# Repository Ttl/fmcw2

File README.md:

FMCW radar hardware, firmware and processing software.

Folders:

hardware: KiCad hardware design files.

- fmcw2: RF board.
- fmcw2_mcu: Digital board.

firmware: 
- Firmware for LPC4320 microcontroller. Based on [HackRF](https://github.com/mossmann/hackrf) firmware.

host: 
- Host programs for recording data, programming firmware. Also from HackRF with small modifications.

processing:
- fir: Resamples, filters and repackages samples for other programs.
- filter.py: Output FIR filter coefficients for fir C program.
- analysis.py: Various analyses about the recorded data.
- sar_bicycle.py: Pre-processing of raw data.
- sar_process.py: Focus raw data to SAR image.
- sar_autofocus.py: Simple minimum entropy autofocusing of SAR image.

SAR focusing program is loosely based on Matlab program by Gregory L. Charvat
and it also includes some functions from [RITSAR](https://github.com/dm6718/RITSAR).

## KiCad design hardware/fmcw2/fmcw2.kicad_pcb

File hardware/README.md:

PCB info:

OSH Park 4-layer.

Material: FR408

Relative permittivity: 3.66

Tangent delta: 0.0127

Stackup:

- 1 mil solder resist
- 1 oz copper (1.4 mil)
- 6.7 mil prepreg
- 0.5 oz copper (0.7 mil)
- 47 mil core
- 0.5 oz copper (0.7 mil)
- 6.7 mil prepreg
- 1 oz copper (1.4 mil)
- 1 mil solder resist

More information: http://support.oshpark.com/support/solutions/articles/122263-4-layer-board-stackup-and-specifications

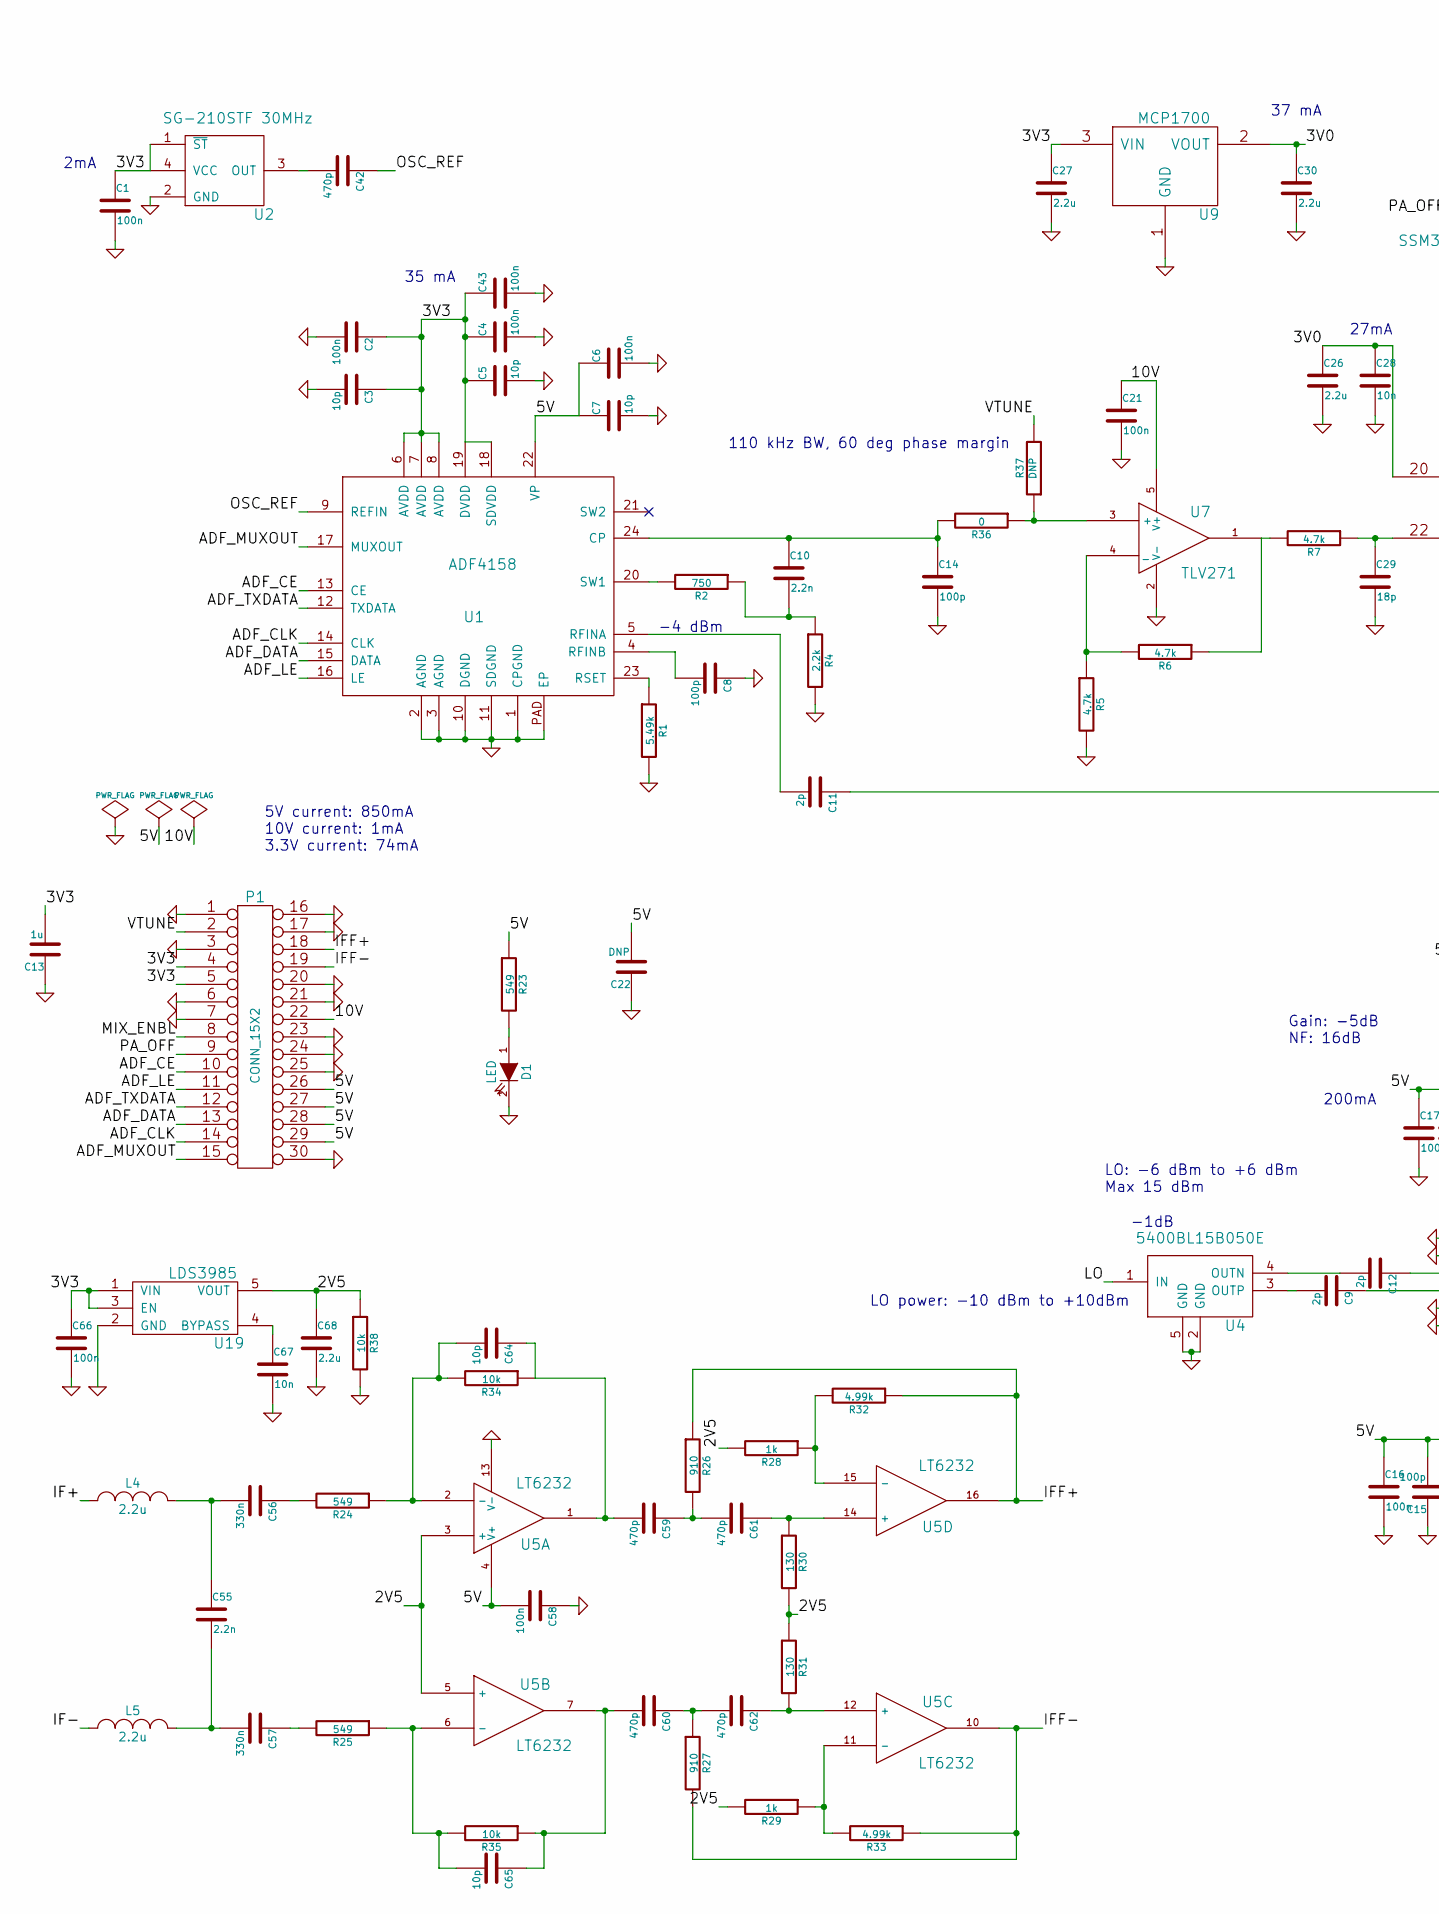
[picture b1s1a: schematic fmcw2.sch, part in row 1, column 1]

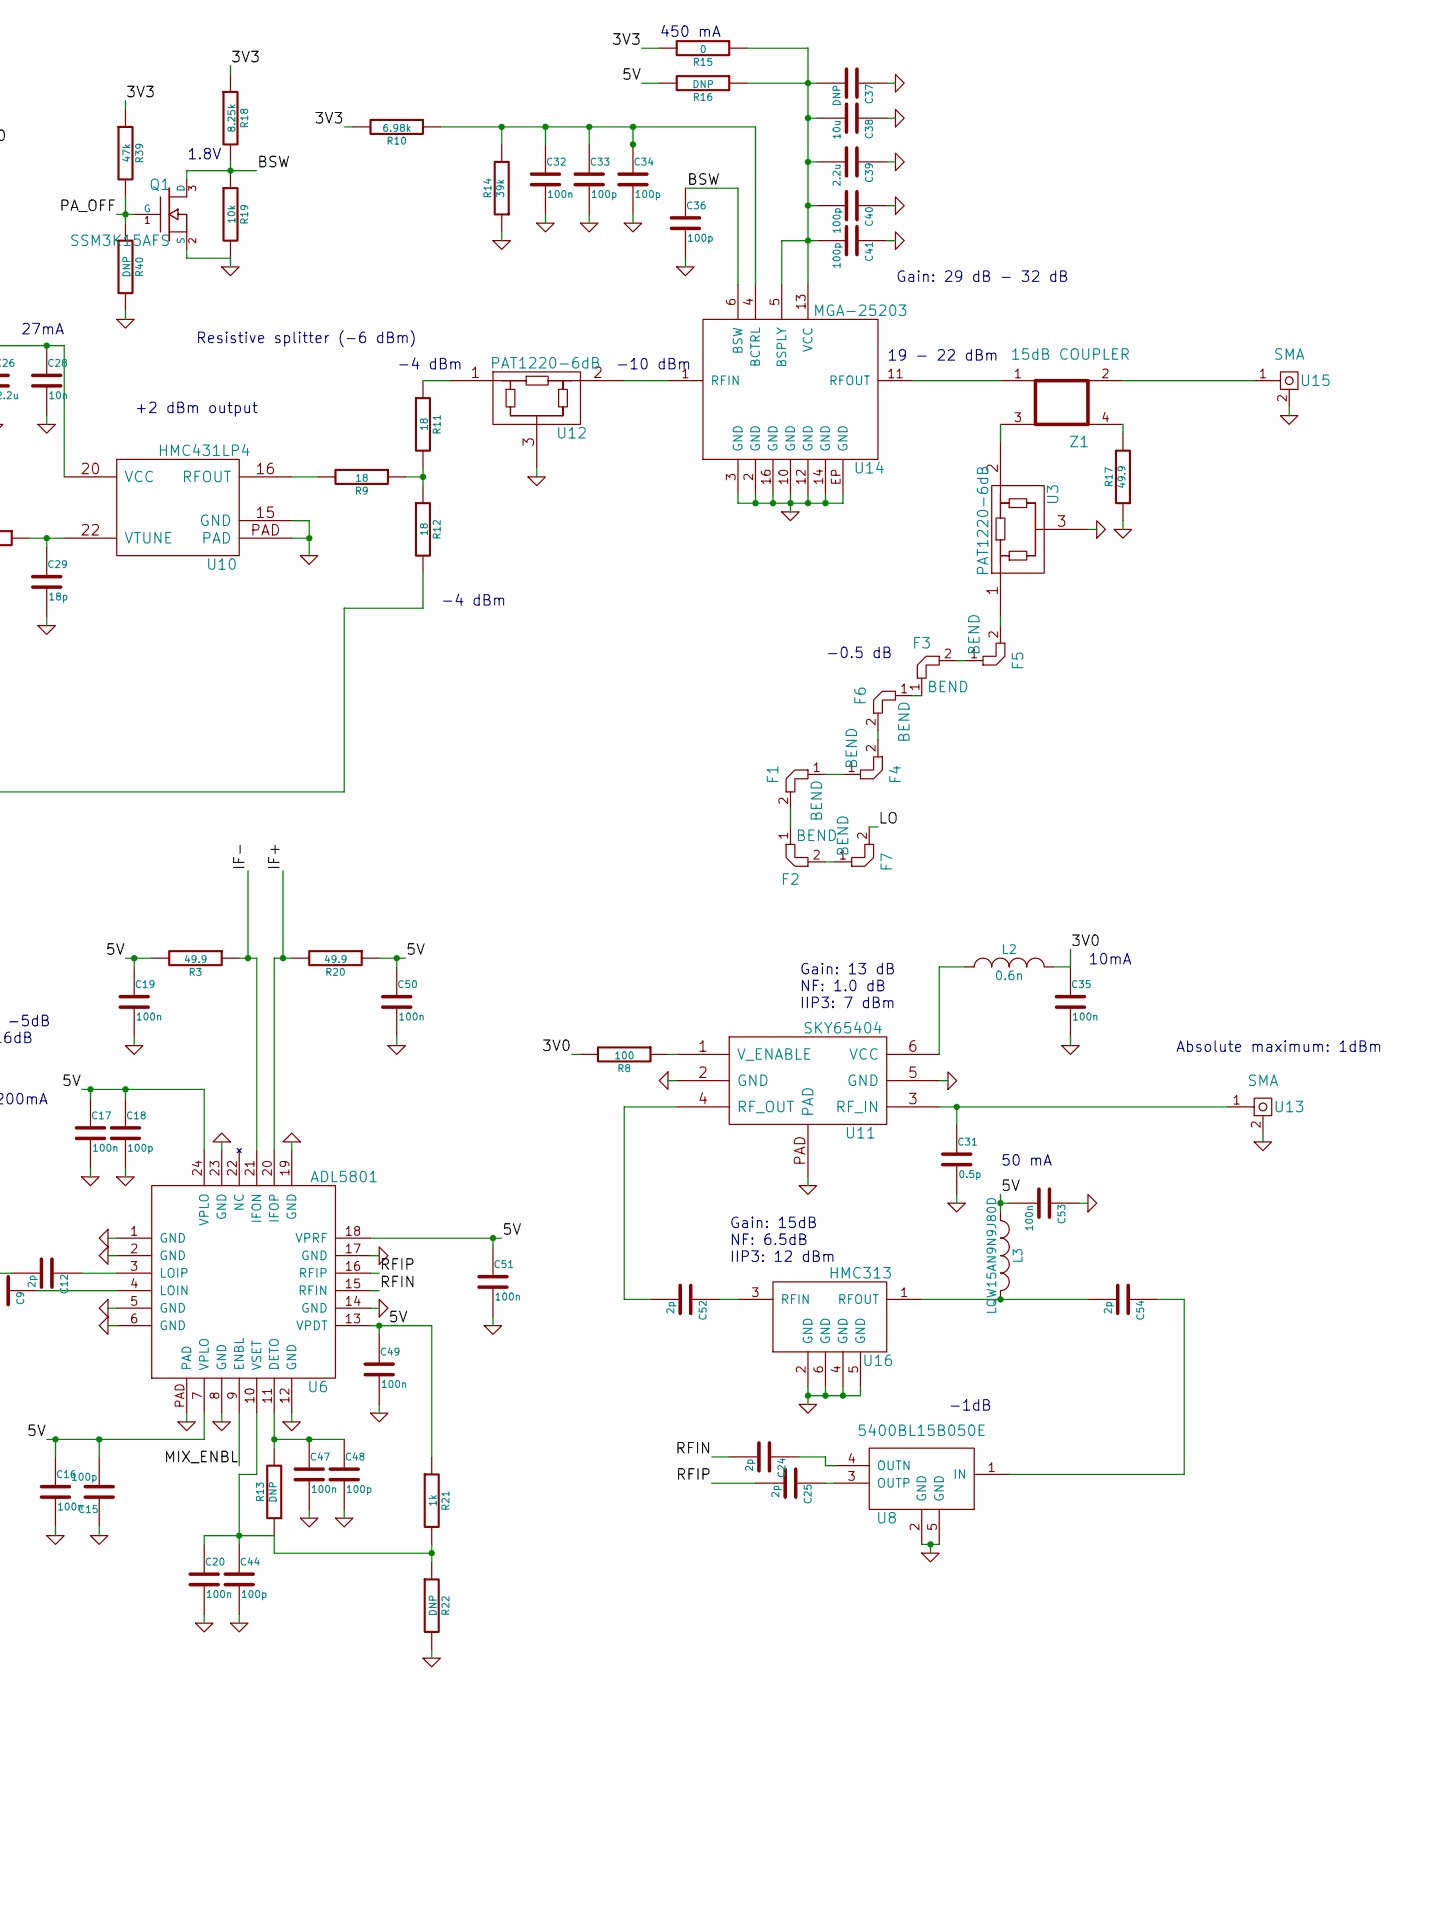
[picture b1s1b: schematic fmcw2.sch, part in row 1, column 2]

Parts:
C1, C2, C4, C6, C16, C17, C19, C20, C21, C32, C35, C43, C47, C49, C50, C51, C53, C58, C66: 100n; C_0402b
C3, C5, C7, C64, C65: 10p; C_0402b
C8, C14, C15, C18, C33, C34, C36, C40, C41, C44, C48: 100p; C_0402b
C9, C11, C12, C24, C25, C52, C54: 2p; C_0402b
C10, C55: 2.2n; C_0402b
C13: 1u; C_0603b
C22: DNP; C_0805b
C26, C27, C30, C39, C68: 2.2u; C_0603b
C28, C67: 10n; C_0402b
C29: 18p; C_0402b
C31: 0.5p; C_0402b
C37: DNP; C_0603b
C38: 10u; C_0805b
C42, C59, C60, C61, C62: 470p; C_0402b
C56, C57: 330n; C_0603b
D1: LED; LED_0603
F1, F2, F7: BEND; uwmiter_0.34_0.17_90
F3, F4, F5, F6: BEND; uwmiter_0.34_0.17_45
L2: 0.6n; C_0402
L3: LQW15AN9N9J80D; C_0402
L4, L5: 2.2u; C_0402
P1: CONN_15X2; DF12B(5.0)-30DP-0.5V(86)
Q1: SSM3K15AFS; SOT-416
R1: 5.49k; R_0402b
R2: 750; R_0402b
R3, R17, R20: 49.9; R_0402b
R4: 2.2k; R_0402b
R5, R6, R7: 4.7k; R_0402b
R8: 100; R_0402b
R9, R11, R12: 18; R_0402b
R10: 6.98k; R_0402b
R13, R16, R22, R37, R40: DNP; R_0402b
R14: 39k; R_0402b
R15, R36: 0; R_0402b
R18: 8.25k; R_0402b
R19, R34, R35, R38: 10k; R_0402b
R21, R28, R29: 1k; R_0402b
R23, R24, R25: 549; R_0402b
R26, R27: 910; R_0402b
R30, R31: 130; R_0402b
R32, R33: 4.99k; R_0402b
R39: 47k; R_0402b
U1: ADF4158; VFQFN-24
U2: SG-210STF 30MHz; SG-210STF
U3, U12: PAT1220-6dB; PAT1220
U4, U8: 5400BL15B050E
U5: LT6232; SSOP-16_3.9x4.9mm_Pitch0.635mm
U6: ADL5801; VFQFN-24
U7: TLV271; SOT-23-5
U9: MCP1700; SOT-23
U10: HMC431LP4; VQFN-24
U11: SKY65404; XFDFN-6
U13, U15: SMA; CONSMA003.062
U14: MGA-25203
U16: HMC313; SOT-23-6
U19: LDS3985; SOT-23-5L
Z1: 15dB COUPLER; coupler

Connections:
/2V5: C68.1, R28.2, R29.2, R30.2, R31.1, R38.1, U5.3 (+), U5.5 (+), U19.5 (VOUT)
/3V0: C26.1, C28.1, C30.1, C35.1, L2.2, R8.2, U9.2 (VOUT), U10.20 (VCC)
/3V3: C1.1, C2.1, C3.1, C4.1, C5.1, C13.2, C27.1, C43.1, C66.1, P1.4, P1.5, R10.2, R15.2, R18.1, R39.1, U1.6 (AVDD), U1.7 (AVDD), U1.8 (AVDD), U1.18 (SDVDD), U1.19 (DVDD), U2.1 (~ST), U2.4 (VCC), U9.3 (VIN), U19.1 (VIN), U19.3 (EN)
/5V: C6.1, C7.1, C15.2, C16.1, C17.1, C18.1, C19.1, C22.2, C49.1, C50.1, C51.1, C53.2, C58.2, L3.1, P1.26, P1.27, P1.28, P1.29, R3.2, R16.2, R20.1, R21.1, R23.1, U1.22 (VP), U5.4 (V+), U6.7 (VPLO), U6.13 (VPDT), U6.18 (VPRF), U6.24 (VPLO)
/10V: C21.1, P1.22, U7.5 (V+)
/ADF_CE: P1.10, U1.13 (CE)
/ADF_CLK: P1.14, U1.14 (CLK)
/ADF_DATA: P1.13, U1.15 (DATA)
/ADF_LE: P1.11, U1.16 (LE)
/ADF_MUXOUT: P1.15, U1.17 (MUXOUT)
/ADF_TXDATA: P1.12, U1.12 (TXDATA)
/BSW: C36.1, Q1.3 (D), R18.2, R19.1, U14.6 (BSW)
/IF+: L4.1, R20.2, U6.20 (IFOP)
/IF-: L5.1, R3.1, U6.21 (IFON)
/IFF+: P1.18, R26.1, R32.1, U5.16
/IFF-: P1.19, R27.2, R33.1, U5.10
/LO: F7.2, U4.1 (IN)
/MIX_ENBL: P1.8, U6.9 (ENBL)
/OSC_REF: C42.1, U1.9 (REFIN)
/PA_OFF: P1.9, Q1.1 (G), R39.2, R40.1
/RFIN: C24.2, U6.15 (RFIN)
/RFIP: C25.2, U6.16 (RFIP)
/VTUNE: P1.2, R37.2
GND: C1.2, C2.2, C3.2, C4.2, C5.2, C6.2, C7.2, C8.1, C13.1, C14.2, C15.1, C16.2, C17.2, C18.2, C19.2, C20.2, C21.2, C22.1, C26.2, C27.2, C28.2, C29.2, C30.2, C31.2, C32.2, C33.2, C34.2, C35.2, C36.2, C37.1, C38.1, C39.1, C40.1, C41.1, C43.2, C44.2, C47.2, C48.2, C49.2, C50.2, C51.2, C53.1, C58.1, C66.2, C67.2, C68.2, D1.2 (K), P1.1, P1.3, P1.6, P1.7, P1.16, P1.17, P1.20, P1.21, P1.23, P1.24, P1.25, P1.30, Q1.2 (S), R1.2, R4.2, R5.2, R14.1, R17.1, R19.2, R22.2, R38.2, R40.2, U1.1 (CPGND), U1.2 (AGND), U1.3 (AGND), U1.10 (DGND), U1.11 (SDGND), U1.PAD (EP), U2.2 (GND), U3.3, U4.2 (GND), U4.5 (GND), U5.13 (V-), U6.1 (GND), U6.2 (GND), U6.5 (GND), U6.6 (GND), U6.8 (GND), U6.12 (GND), U6.14 (GND), U6.17 (GND), U6.19 (GND), U6.23 (GND), U6.PAD, U7.2 (V-), U8.2 (GND), U8.5 (GND), U9.1 (GND), U10.15 (GND), U10.PAD, U11.2 (GND), U11.5 (GND), U11.PAD, U12.3, U13.2, U14.2 (GND), U14.3 (GND), U14.10 (GND), U14.12 (GND), U14.14 (GND), U14.16 (GND), U14.EP (GND), U15.2, U16.2 (GND), U16.4 (GND), U16.5 (GND), U16.6 (GND), U19.2 (GND)
unnamed: C8.2, U1.4 (RFINB)
unnamed: C9.1, U6.4 (LOIN)
unnamed: C9.2, U4.3 (OUTP)
unnamed: C10.1, C14.1, R36.2, U1.24 (CP)
unnamed: C10.2, R2.1, R4.1
unnamed: C11.1, R12.2
unnamed: C11.2, U1.5 (RFINA)
unnamed: C12.1, U6.3 (LOIP)
unnamed: C12.2, U4.4 (OUTN)
unnamed: C20.1, C44.1, R13.1, R21.2, R22.1, U6.10 (VSET)
unnamed: C24.1, U8.4 (OUTN)
unnamed: C25.1, U8.3 (OUTP)
unnamed: C29.1, R7.1, U10.22 (VTUNE)
unnamed: C31.1, U11.3 (RF_IN), U13.1
unnamed: C32.1, C33.1, C34.1, R10.1, R14.2, U14.4 (BCTRL)
unnamed: C37.2, C38.2, C39.2, C40.2, C41.2, R15.1, R16.1, U14.5 (BSPLY), U14.13 (VCC)
unnamed: C42.2, U2.3 (OUT)
unnamed: C47.1, C48.1, R13.2, U6.11 (DETO)
unnamed: C52.1, U16.3 (RFIN)
unnamed: C52.2, U11.4 (RF_OUT)
unnamed: C54.1, U8.1 (IN)
unnamed: C54.2, L3.2, U16.1 (RFOUT)
unnamed: C55.1, C56.2, L4.2
unnamed: C55.2, C57.2, L5.2
unnamed: C56.1, R24.2
unnamed: C57.1, R25.2
unnamed: C59.1, C61.2, R26.2
unnamed: C59.2, C64.1, R34.1, U5.1
unnamed: C60.1, C62.2, R27.1
unnamed: C60.2, C65.1, R35.1, U5.7
unnamed: C61.1, R30.1, U5.14 (+)
unnamed: C62.1, R31.2, U5.12 (+)
unnamed: C64.2, R24.1, R34.2, U5.2 (-)
unnamed: C65.2, R25.1, R35.2, U5.6 (-)
unnamed: C67.1, U19.4 (BYPASS)
unnamed: D1.1 (A), R23.2
unnamed: F1.1, F4.1
unnamed: F1.2, F2.1
unnamed: F2.2, F7.1
unnamed: F3.1, F6.1
unnamed: F3.2, F5.1
unnamed: F4.2, F6.2
unnamed: F5.2, U3.1
unnamed: L2.1, U11.6 (VCC)
unnamed: R1.1, U1.23 (RSET)
unnamed: R2.2, U1.20 (SW1)
unnamed: R5.1, R6.2, U7.4 (_)
unnamed: R6.1, R7.2, U7.1
unnamed: R8.1, U11.1 (V_ENABLE)
unnamed: R9.2, U10.16 (RFOUT)
unnamed: R11.1, U12.1
unnamed: R9.1, R11.2, R12.1
unnamed: R17.2, Z1.4
unnamed: R28.1, R32.2, U5.15 (-)
unnamed: R29.1, R33.2, U5.11 (-)
unnamed: R36.1, R37.1, U7.3 (+)
unnamed: U3.2, Z1.3
unnamed: U12.2, U14.1 (RFIN)
unnamed: U14.11 (RFOUT), Z1.1
unnamed: U15.1, Z1.2

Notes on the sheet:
Resistive splitter (-6 dBm)
+2 dBm output
-4 dBm
27mA
-10 dBm
Gain: 29 dB - 32 dB
19 - 22 dBm
110 kHz BW, 60 deg phase margin
2mA
LO: -6 dBm to +6 dBm Max 15 dBm
35 mA
450 mA
10mA
37 mA
-1dB
1.8V
Gain: 13 dB NF: 1.0 dB IIP3: 7 dBm
Gain: -5dB NF: 16dB
200mA
LO power: -10 dBm to +10dBm
Gain: 15dB NF: 6.5dB IIP3: 12 dBm
50 mA
Absolute maximum: 1dBm
5V current: 850mA 10V current: 1mA 3.3V current: 74mA
-0.5 dB

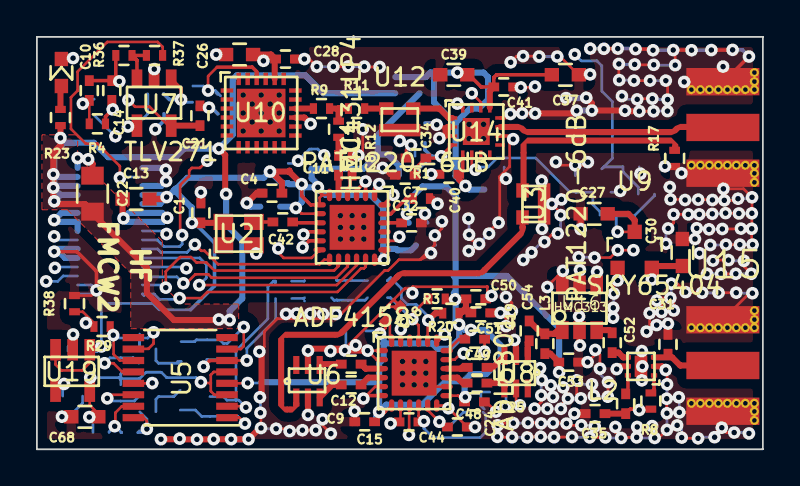
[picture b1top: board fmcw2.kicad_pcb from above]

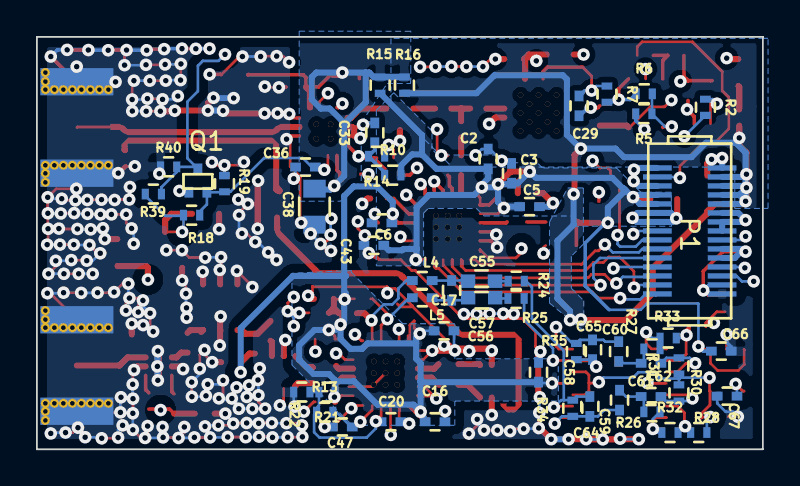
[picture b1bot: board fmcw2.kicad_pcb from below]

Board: 4 copper layers, 40.3 x 22.9 mm, 136 parts (55 on the bottom side), 84 nets.

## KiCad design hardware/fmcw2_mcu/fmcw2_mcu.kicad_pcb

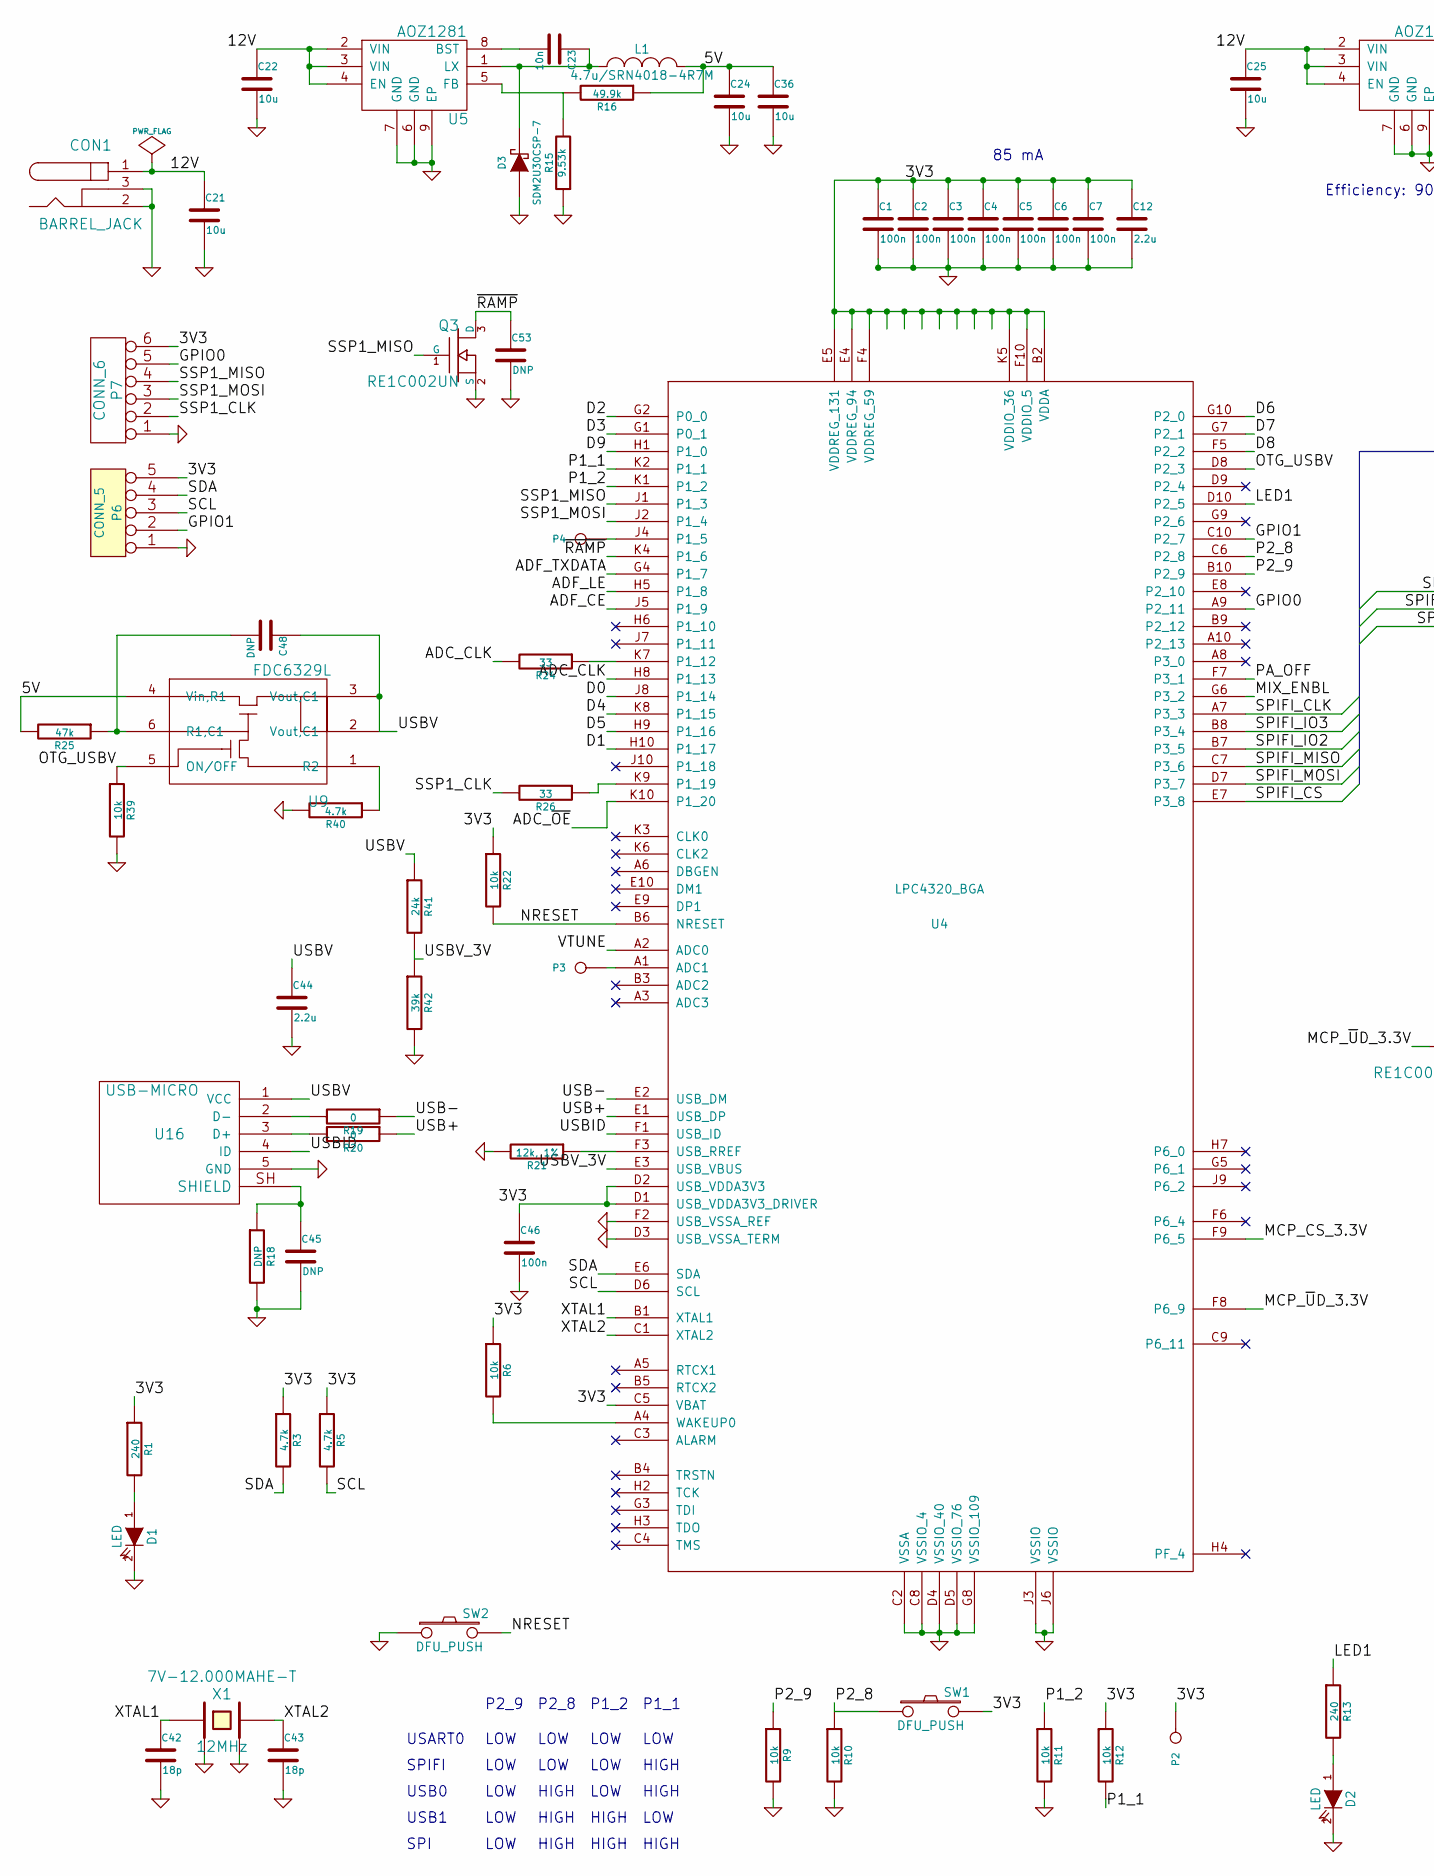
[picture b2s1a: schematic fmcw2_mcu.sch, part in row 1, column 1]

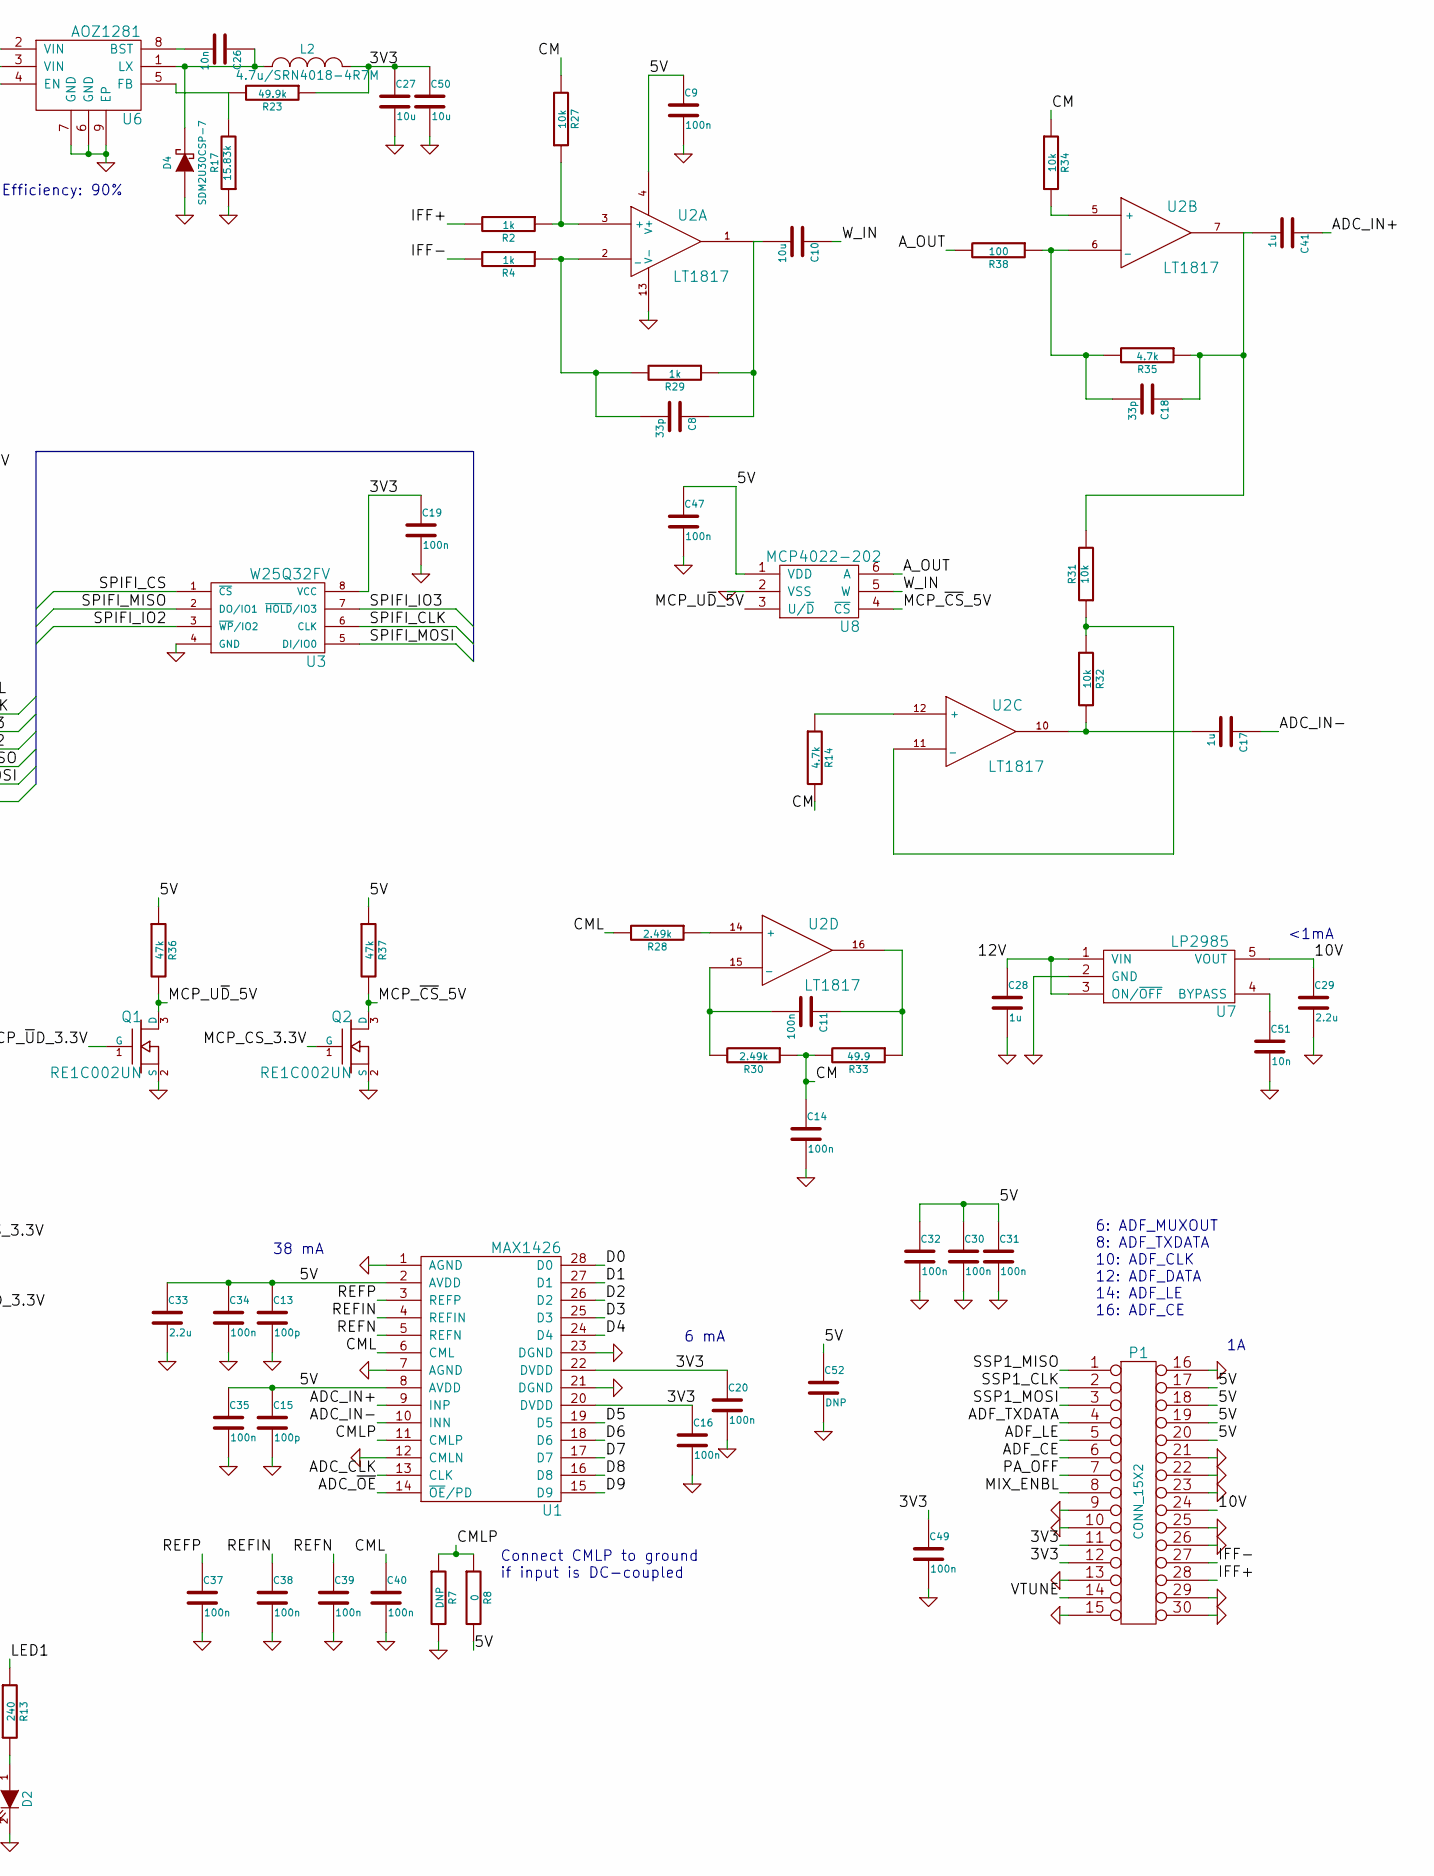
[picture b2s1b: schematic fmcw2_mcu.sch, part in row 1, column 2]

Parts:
C1, C2, C3, C4, C5, C6, C7, C9, C11, C14, C16, C19, C20, C30, C31, C32, C34, C35, C37, C38, C39, C40, C46, C47, C49: 100n; C_0402b
C8, C18: 33p; C_0402b
C10, C21, C22, C24, C25, C27, C36, C50: 10u; C_0805b
C12, C29, C33, C44: 2.2u; C_0603b
C13, C15: 100p; C_0402b
C17, C28, C41: 1u; C_0603b
C23, C26, C51: 10n; C_0402b
C42, C43: 18p; C_0402b
C45, C48, C53: DNP; C_0402b
C52: DNP; C_0603b
CON1: BARREL_JACK; EJ508A
D1, D2: LED; LED_0603
D3, D4: SDM2U30CSP-7; XDFN-2
L1, L2: 4.7u/SRN4018-4R7M; SRN4018
P1: CONN_15X2; DF12A-30DS-0.5V(81)
P2, P3, P4: CONN_1; TP_1.00
P6: CONN_5; Pin_Header_Straight_1x05
P7: CONN_6; Pin_Header_Straight_1x06
Q1, Q2, Q3: RE1C002UN; SOT-416
R1, R13: 240; R_0402b
R2, R4, R29: 1k; R_0402b
R3, R5, R14, R35, R40: 4.7k; R_0402b
R6, R9, R10, R11, R12, R22, R27, R31, R32, R34, R39: 10k; R_0402b
R7, R18: DNP; R_0402b
R8, R19, R20: 0; R_0402b
R15: 9.53k; R_0402b
R16, R23: 49.9k; R_0402b
R17: 15.83k; R_0402b
R21: 12k, 1%; R_0402b
R24, R26: 33; R_0402b
R25, R36, R37: 47k; R_0402b
R28, R30: 2.49k; R_0402b
R33: 49.9; R_0402b
R38: 100; R_0402b
R41: 24k; R_0402b
R42: 39k; R_0402b
SW1, SW2: DFU_PUSH; EVP-AWBA2A
U1: MAX1426; SSOP-28_5.3x10.2mm_Pitch0.65mm
U2: LT1817; SSOP-16_3.9x4.9mm_Pitch0.635mm
U3: W25Q32FV; SOIJ-8_5.3x5.3mm_Pitch1.27mm
U4: LPC4320_BGA; TFBGA-100
U5, U6: AOZ1281; WFDFN-8
U7: LP2985; SOT-23-5
U8: MCP4022-202; SOT-23-6
U9: FDC6329L; SSOT-6
U16: USB-MICRO; USB_MICRO
X1: 12MHz; XTAL_3.2x2.5

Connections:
/3V3: C1.1, C2.1, C3.1, C4.1, C5.1, C6.1, C7.1, C12.1, C16.1, C19.1, C20.1, C27.1, C46.1, C49.1, C50.1, L2.2, P1.11, P1.12, P2.1, P6.5, P7.6, R1.1, R3.1, R5.1, R6.1, R12.1, R22.1, R23.1, SW1.2, U1.20 (DVDD), U1.22 (DVDD), U3.8 (VCC), U4.B2 (VDDA), U4.C5 (VBAT), U4.D1 (USB_VDDA3V3_DRIVER), U4.D2 (USB_VDDA3V3), U4.E4 (VDDREG_94), U4.E5 (VDDREG_131), U4.F4 (VDDREG_59), U4.F10 (VDDIO_5), U4.K5 (VDDIO_36)
/5V: C9.1, C13.1, C15.1, C24.1, C30.1, C31.1, C32.1, C33.1, C34.1, C35.1, C36.1, C47.1, C52.1, L1.2, P1.17, P1.18, P1.19, P1.20, R8.2, R16.1, R25.2, R36.1, R37.1, U1.2 (AVDD), U1.8 (AVDD), U2.4 (V+), U8.1 (VDD), U9.4 (Vin,R1)
/10V: C29.1, P1.24, U7.5 (VOUT)
/12V: C21.1, C22.1, C25.1, C28.1, CON1.1, U5.2 (VIN), U5.3 (VIN), U5.4 (EN), U6.2 (VIN), U6.3 (VIN), U6.4 (EN), U7.1 (VIN), U7.3 (ON/~OFF~)
/ADC_CLK: R24.2, U1.13 (CLK), U4.H8 (P1_13)
/ADC_IN+: C41.1, U1.9 (INP)
/ADC_IN-: C17.1, U1.10 (INN)
/ADC_~OE~: U1.14 (~OE~/PD), U4.K10 (P1_20)
/ADF_CE: P1.6, U4.J5 (P1_9)
/ADF_LE: P1.5, U4.H5 (P1_8)
/ADF_TXDATA: P1.4, U4.G4 (P1_7)
/A_OUT: R38.2, U8.6 (A)
/CM: C14.1, R14.2, R27.2, R30.1, R33.2, R34.1
/CML: C40.1, R28.2, U1.6 (CML)
/CMLP: R7.1, R8.1, U1.11 (CMLP)
/D0: U1.28 (D0), U4.J8 (P1_14)
/D1: U1.27 (D1), U4.H10 (P1_17)
/D2: U1.26 (D2), U4.G2 (P0_0)
/D3: U1.25 (D3), U4.G1 (P0_1)
/D4: U1.24 (D4), U4.K8 (P1_15)
/D5: U1.19 (D5), U4.H9 (P1_16)
/D6: U1.18 (D6), U4.G10 (P2_0)
/D7: U1.17 (D7), U4.G7 (P2_1)
/D8: U1.16 (D8), U4.F5 (P2_2)
/D9: U1.15 (D9), U4.H1 (P1_0)
/GPIO0: P7.5, U4.A9 (P2_11)
/GPIO1: P6.2, U4.C10 (P2_7)
/IFF+: P1.28, R2.2
/IFF-: P1.27, R4.2
/LED1: R13.1, U4.D10 (P2_5)
/MCP_CS_3.3V: Q2.1 (G), U4.F9 (P6_5)
/MCP_U~D~_5V: Q1.3 (D), R36.2, U8.3 (U/~D~)
/MCP_~CS~_5V: Q2.3 (D), R37.2, U8.4 (~CS~)
/MCP_~U~D_3.3V: Q1.1 (G), U4.F8 (P6_9)
/MIX_ENBL: P1.8, U4.G6 (P3_2)
/NRESET: R22.2, SW2.2, U4.B6 (NRESET)
/OTG_USBV: R39.1, U4.D8 (P2_3), U9.5 (ON/OFF)
/P1_1: R12.2, U4.K2 (P1_1)
/P1_2: R11.1, U4.K1 (P1_2)
/P2_8: R10.1, SW1.1, U4.C6 (P2_8)
/P2_9: R9.1, U4.B10 (P2_9)
/PA_OFF: P1.7, U4.F7 (P3_1)
/REFIN: C38.1, U1.4 (REFIN)
/REFN: C39.1, U1.5 (REFN)
/REFP: C37.1, U1.3 (REFP)
/SCL: P6.3, R5.2, U4.D6 (SCL)
/SDA: P6.4, R3.2, U4.E6 (SDA)
/SPIFI_CLK: U3.6 (CLK), U4.A7 (P3_3)
/SPIFI_CS: U3.1 (~CS), U4.E7 (P3_8)
/SPIFI_IO2: U3.3 (~WP~/IO2), U4.B7 (P3_5)
/SPIFI_IO3: U3.7 (~HOLD~/IO3), U4.B8 (P3_4)
/SPIFI_MISO: U3.2 (DO/IO1), U4.C7 (P3_6)
/SPIFI_MOSI: U3.5 (DI/IO0), U4.D7 (P3_7)
/SSP1_CLK: P1.2, P7.2, R26.2
/SSP1_MISO: P1.1, P7.4, Q3.1 (G), U4.J1 (P1_3)
/SSP1_MOSI: P1.3, P7.3, U4.J2 (P1_4)
/USB+: R20.1, U4.E1 (USB_DP)
/USB-: R19.1, U4.E2 (USB_DM)
/USBID: U4.F1 (USB_ID), U16.4 (ID)
/USBV: C44.1, C48.1, R41.1, U9.2 (Vout,C1), U9.3 (Vout,C1), U16.1 (VCC)
/USBV_3V: R41.2, R42.1, U4.E3 (USB_VBUS)
/VTUNE: P1.14, U4.A2 (ADC0)
/W_IN: C10.1, U8.5 (W)
/XTAL1: C42.1, U4.B1 (XTAL1), X1.1
/XTAL2: C43.1, U4.C1 (XTAL2), X1.3
/~RAMP: C53.1, Q3.3 (D), U4.K4 (P1_6)
GND: C1.2, C2.2, C3.2, C4.2, C5.2, C6.2, C7.2, C9.2, C12.2, C13.2, C14.2, C15.2, C16.2, C19.2, C20.2, C21.2, C22.2, C24.2, C25.2, C27.2, C28.2, C29.2, C30.2, C31.2, C32.2, C33.2, C34.2, C35.2, C36.2, C37.2, C38.2, C39.2, C40.2, C42.2, C43.2, C44.2, C45.2, C46.2, C47.2, C49.2, C50.2, C51.2, C52.2, C53.2, CON1.2, CON1.3, D1.2 (K), D2.2 (K), D3.1 (A), D4.1 (A), P1.9, P1.10, P1.13, P1.15, P1.16, P1.21, P1.22, P1.23, P1.25, P1.26, P1.29, P1.30, P6.1, P7.1, Q1.2 (S), Q2.2 (S), Q3.2 (S), R7.2, R9.2, R10.2, R11.2, R15.1, R17.1, R18.2, R21.2, R39.2, R40.2, R42.2, SW2.1, U1.1 (AGND), U1.7 (AGND), U1.12 (CMLN), U1.21 (DGND), U1.23 (DGND), U2.13 (V-), U3.4 (GND), U4.C2 (VSSA), U4.C8 (VSSIO_4), U4.D3 (USB_VSSA_TERM), U4.D4 (VSSIO_40), U4.D5 (VSSIO_76), U4.F2 (USB_VSSA_REF), U4.G8 (VSSIO_109), U4.J3 (VSSIO), U4.J6 (VSSIO), U5.6 (GND), U5.7 (GND), U5.9 (EP), U6.6 (GND), U6.7 (GND), U6.9 (EP), U7.2 (GND), U8.2 (VSS), U16.5 (GND), X1.2, X1.4
unnamed: C8.2, R4.1, R29.2, U2.2 (_)
unnamed: C8.1, C10.2, R29.1, U2.1
unnamed: C11.1, R33.1, U2.16
unnamed: C11.2, R30.2, U2.15 (_)
unnamed: C17.2, R32.2, U2.10
unnamed: C18.1, C41.2, R31.2, R35.1, U2.7
unnamed: C18.2, R35.2, R38.1, U2.6 (_)
unnamed: C23.1, D3.2 (K), L1.1, U5.1 (LX)
unnamed: C23.2, U5.8 (BST)
unnamed: C26.1, D4.2 (K), L2.1, U6.1 (LX)
unnamed: C26.2, U6.8 (BST)
unnamed: C45.1, R18.1, U16.SH (SHIELD)
unnamed: C48.2, R25.1, U9.6 (R1,C1)
unnamed: C51.1, U7.4 (BYPASS)
unnamed: D1.1 (A), R1.2
unnamed: D2.1 (A), R13.2
unnamed: P3.1, U4.A1 (ADC1)
unnamed: P4.1, U4.J4 (P1_5)
unnamed: R2.1, R27.1, U2.3 (+)
unnamed: R6.2, U4.A4 (WAKEUP0)
unnamed: R14.1, U2.12 (+)
unnamed: R15.2, R16.2, U5.5 (FB)
unnamed: R17.2, R23.2, U6.5 (FB)
unnamed: R19.2, U16.2 (D-)
unnamed: R20.2, U16.3 (D+)
unnamed: R21.1, U4.F3 (USB_RREF)
unnamed: R24.1, U4.K7 (P1_12)
unnamed: R26.1, U4.K9 (P1_19)
unnamed: R28.1, U2.14 (+)
unnamed: R31.1, R32.1, U2.11 (_)
unnamed: R34.2, U2.5 (+)
unnamed: R40.1, U9.1 (R2)

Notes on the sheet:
LOW
P2_9
P2_8
P1_2
P1_1
SPIFI
USART0
HIGH
USB0
USB1
SPI
6: ADF_MUXOUT 8: ADF_TXDATA 10: ADF_CLK 12: ADF_DATA 14: ADF_LE 16: ADF_CE
38 mA
6 mA
Efficiency: 90%
85 mA
<1mA
Connect CMLP to ground if input is DC-coupled

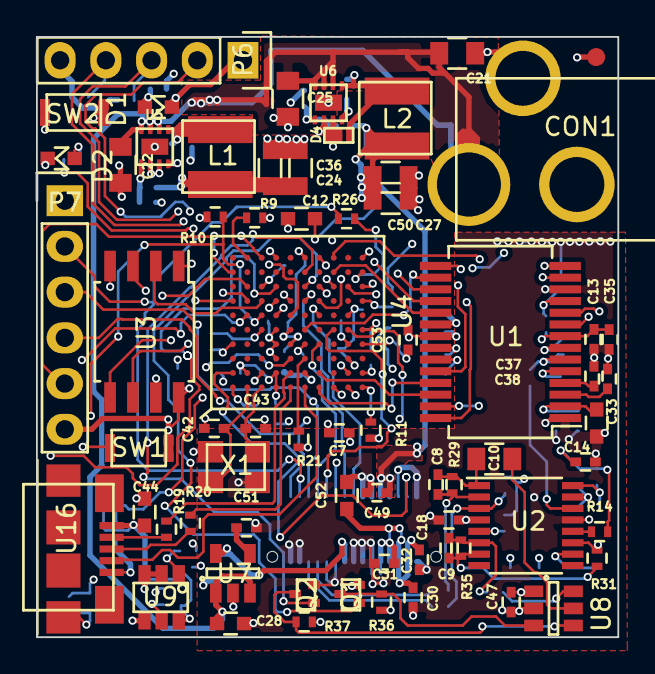
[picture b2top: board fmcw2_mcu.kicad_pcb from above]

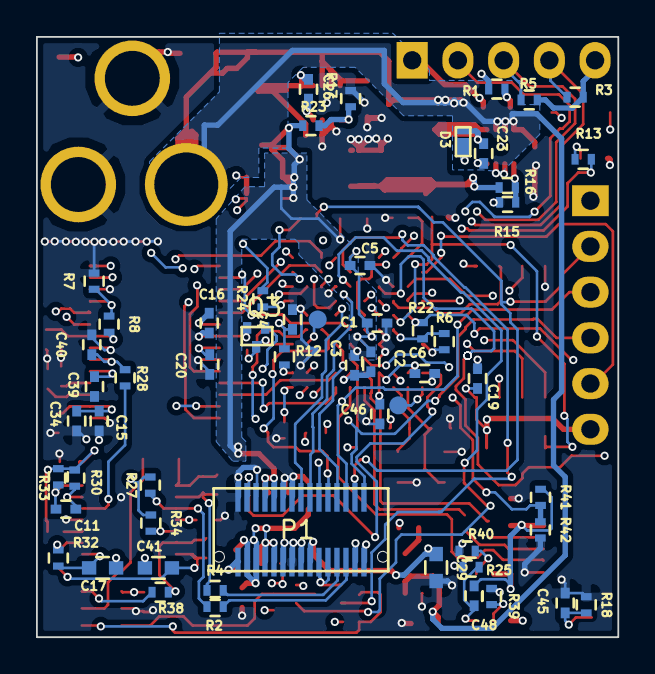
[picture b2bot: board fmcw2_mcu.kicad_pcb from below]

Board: 4 copper layers, 32.3 x 33.3 mm, 124 parts (56 on the bottom side), 99 nets.

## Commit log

2015-07-23 Initial firmware commit
2015-07-27 PC GUI initial commit
2015-07-27 Use pyqtgraph for plotting
2015-07-28 Big plot for range
2015-08-10 Add gitignore
2015-08-10 Update PC program
    Menus, new architecture, add old FMCW radar
2015-08-16 Update firmware
2015-08-18 Add python scripts
2015-08-29 Use all 10bits from ADC
    Add some forgotten files.
2015-08-29 Add C tools
2015-08-29 Add filtering + decimation tool
2015-08-29 Fix filtering script
2015-08-30 Update processing scripts for sync bits
2015-08-30 Send sync words
    Needs jump wire from SSP1_MISO to P5.
    Uses the ramp complete signal from ADF4158 to synchronize the ramps.
2015-09-06 Update processing programs
    Multithreaded file writing in transfer program
    Add header to saved files
    Enable pullup in ramp complete input pin
2015-09-12 Fix off-by-one mistake causing data corruption
2015-10-13 Update various files
2015-10-13 Add hardware design files
2015-10-13 Add program for finding sweeps with invalid length
2015-10-13 Add program for processing bicycle SAR data
2015-10-13 Add SAR focusing program
2015-10-13 Add SAR autofocusing program
2015-10-13 Remove unused GUI, move fir program to processing folder
2015-10-13 Add PDF of schematic
2015-10-14 Add Readme
2015-10-14 Fix Readme formatting
2015-10-14 Fix Readme formatting again
2015-10-14 Fix formatting in hardware readme
2015-11-09 Rescue schematic symbols to a new library
    Schematic used old symbols and without cached library files
    uses instead the new symbols that have different pin pitch.
2015-11-09 Add jump wire transistor
    Scretches the ramp complete pulse from ADF4158.
    Internal pull-up resistor of the microcontroller pin is used
    to pull-up the transistor drain.
2016-01-16 Change inductors to better shielded ones
    Previous inductors weren't too well shielded and radiated a lot.
    Footprint is unchanged.
    R27 is also changed to 1k from 10k to increase PSRR.
2016-01-16 Add sweep delay to setup and default to sawtooth waveform
2016-01-16 Increase PLL loop bandwidth
    Faster frequency settling
2016-01-16 Add command line options
2016-01-16 Clean code
2016-03-09 Improve SMA connector footprint
    Better matching than the previous one.
2016-07-13 Add missing cmake folder in host directory
2016-07-13 Update analysis.py file
    Handles new header.
    Cleaning.
    Other small improvements.
2016-07-13 Add missing files
2016-07-13 Add libopencm3 folder
2016-12-22 Disable baseband filter compensation code
